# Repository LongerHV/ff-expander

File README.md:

# FF expander

ff-expander is a wireless expansion module for ffbeast based steering wheels.

Two Seeed XIAO ESP32-C6 boards linked over ESP-NOW: the **tx** board in the
wheel reads up to 10 buttons; the **rx** board in the base drives the parallel
inputs of two daisy-chained 74HC165s, which the MKS XDRIVE MINI reads over SPI.
Design notes: `docs/superpowers/specs/2026-11-23-ff-expander-design.md`.

## Wiring

| Button | TX pad (to GND) | RX pad (→ 74HC165) |
|-------:|-----------------|--------------------|
| 0 | D1 (wake) | D0 → chip 1 A |
| 1 | D2 (wake) | D1 → chip 1 B |
| 2 | D3 | D2 → chip 1 C |
| 3 | D4 | D3 → chip 1 D |
| 4 | D5 | D4 → chip 1 E |
| 5 | D6 | D5 → chip 1 F |
| 6 | D7 | D10 → chip 1 G |
| 7 | D8 | D7 → chip 1 H |
| 8 | D9 | D8 → chip 2 A |
| 9 | D10 | D9 → chip 2 B |

- TX buttons are wired between the pad and GND (internal pull-ups). D0 is free
  for a future battery-voltage divider. Buttons 0/1 wake the wheel from sleep.
- RX outputs are **low when pressed**, high when released or when the link is
  lost (`FFX_RX_PRESSED_LOW` in `include/ffx_config.h`). Tie unused 165 inputs
  high. Power the 165s from **3.3 V**.
- The RX user LED is lit while the link is up; the TX sleeps after 10 min idle.

### Proof of concept (no PCBs)

Envs `tx-poc` / `rx-poc` (`-DFFX_POC=1`) build a 4-button variant with the RX
wired straight to XDRIVE GPIO inputs, no 74HC165s:

| Button | TX pad (to GND) | RX pad → XDRIVE |
|-------:|-----------------|-----------------|
| 0 | D1 (wake) | D0 ─1k─► GPIO input |
| 1 | D2 (wake) | D1 ─1k─► GPIO input |
| 2 | D3 | D2 ─1k─► GPIO input |
| 3 | D4 | D3 ─1k─► GPIO input |

- XDRIVE inputs use their internal pull-ups, configured active-low. Check that
  they read released (> ~2.3 V) while the XIAO is held in its bootloader;
  otherwise add 10k pull-ups to 3V3.
- Power: header +5V → Schottky (SS14 / 1N5817) → XIAO `5V`, plus GND. The
  diode stops USB and the XDRIVE back-feeding each other.
- `python3 tools/link_test.py --buttons 4`

## Build, flash, test

```sh
nix develop                 # or nix-shell
pio test -e native          # unit tests for lib/ffx_core
pio run -e tx -t upload     # wheel board
pio run -e rx -t upload     # base board
python3 tools/link_test.py  # end-to-end test with both boards on USB
tools/lint.sh               # clang-format, ruff, nixfmt, actionlint
tools/check_hardware.sh     # generators in sync, ERC, DRC
```

CI (`.github/workflows/ci.yml`) runs the lint, unit tests, firmware build and
hardware checks on every push to `master` and on pull requests.

### Releases

Push a semver tag (`v1.2.3`, or `v1.2.3-rc.1` for a pre-release). The release
workflow reruns CI, then publishes a GitHub release with:

- `ff-expander-<tag>-tx.bin`, `ff-expander-<tag>-rx.bin`: complete flash
  images, written at offset 0:
  `esptool --chip esp32c6 write-flash 0x0 ff-expander-<tag>-tx.bin`
- `ff-expander-<tag>-{tx,rx}-gerbers.zip`: gerbers and drill files.

The same artifacts build locally with `tools/release.sh <version> dist`.

Board MACs (pairing) and serial ports are set in `include/ffx_config.h` and
`platformio.ini`.

### Console commands

TX: `p N` / `r N` press/release simulated button N, `m MASK` set all simulated
buttons, `mute MS` stop transmitting, `s` stats, `sleep`, `reboot`.
RX: `s` link stats. RX logs every output change as `RX t=… btn=0x… link=up|down`.

## License

- **Firmware, tools and scripts** (including `hardware/*.py`): MIT — see
  [LICENSE](LICENSE).
- **Hardware design** (`hardware/` KiCad files and libraries in `hardware/lib/`,
  `docs/hardware.md`): CERN Open Hardware Licence v2 – Strongly Reciprocal
  (CERN-OHL-S-2.0) — see [hardware/LICENSE](hardware/LICENSE).

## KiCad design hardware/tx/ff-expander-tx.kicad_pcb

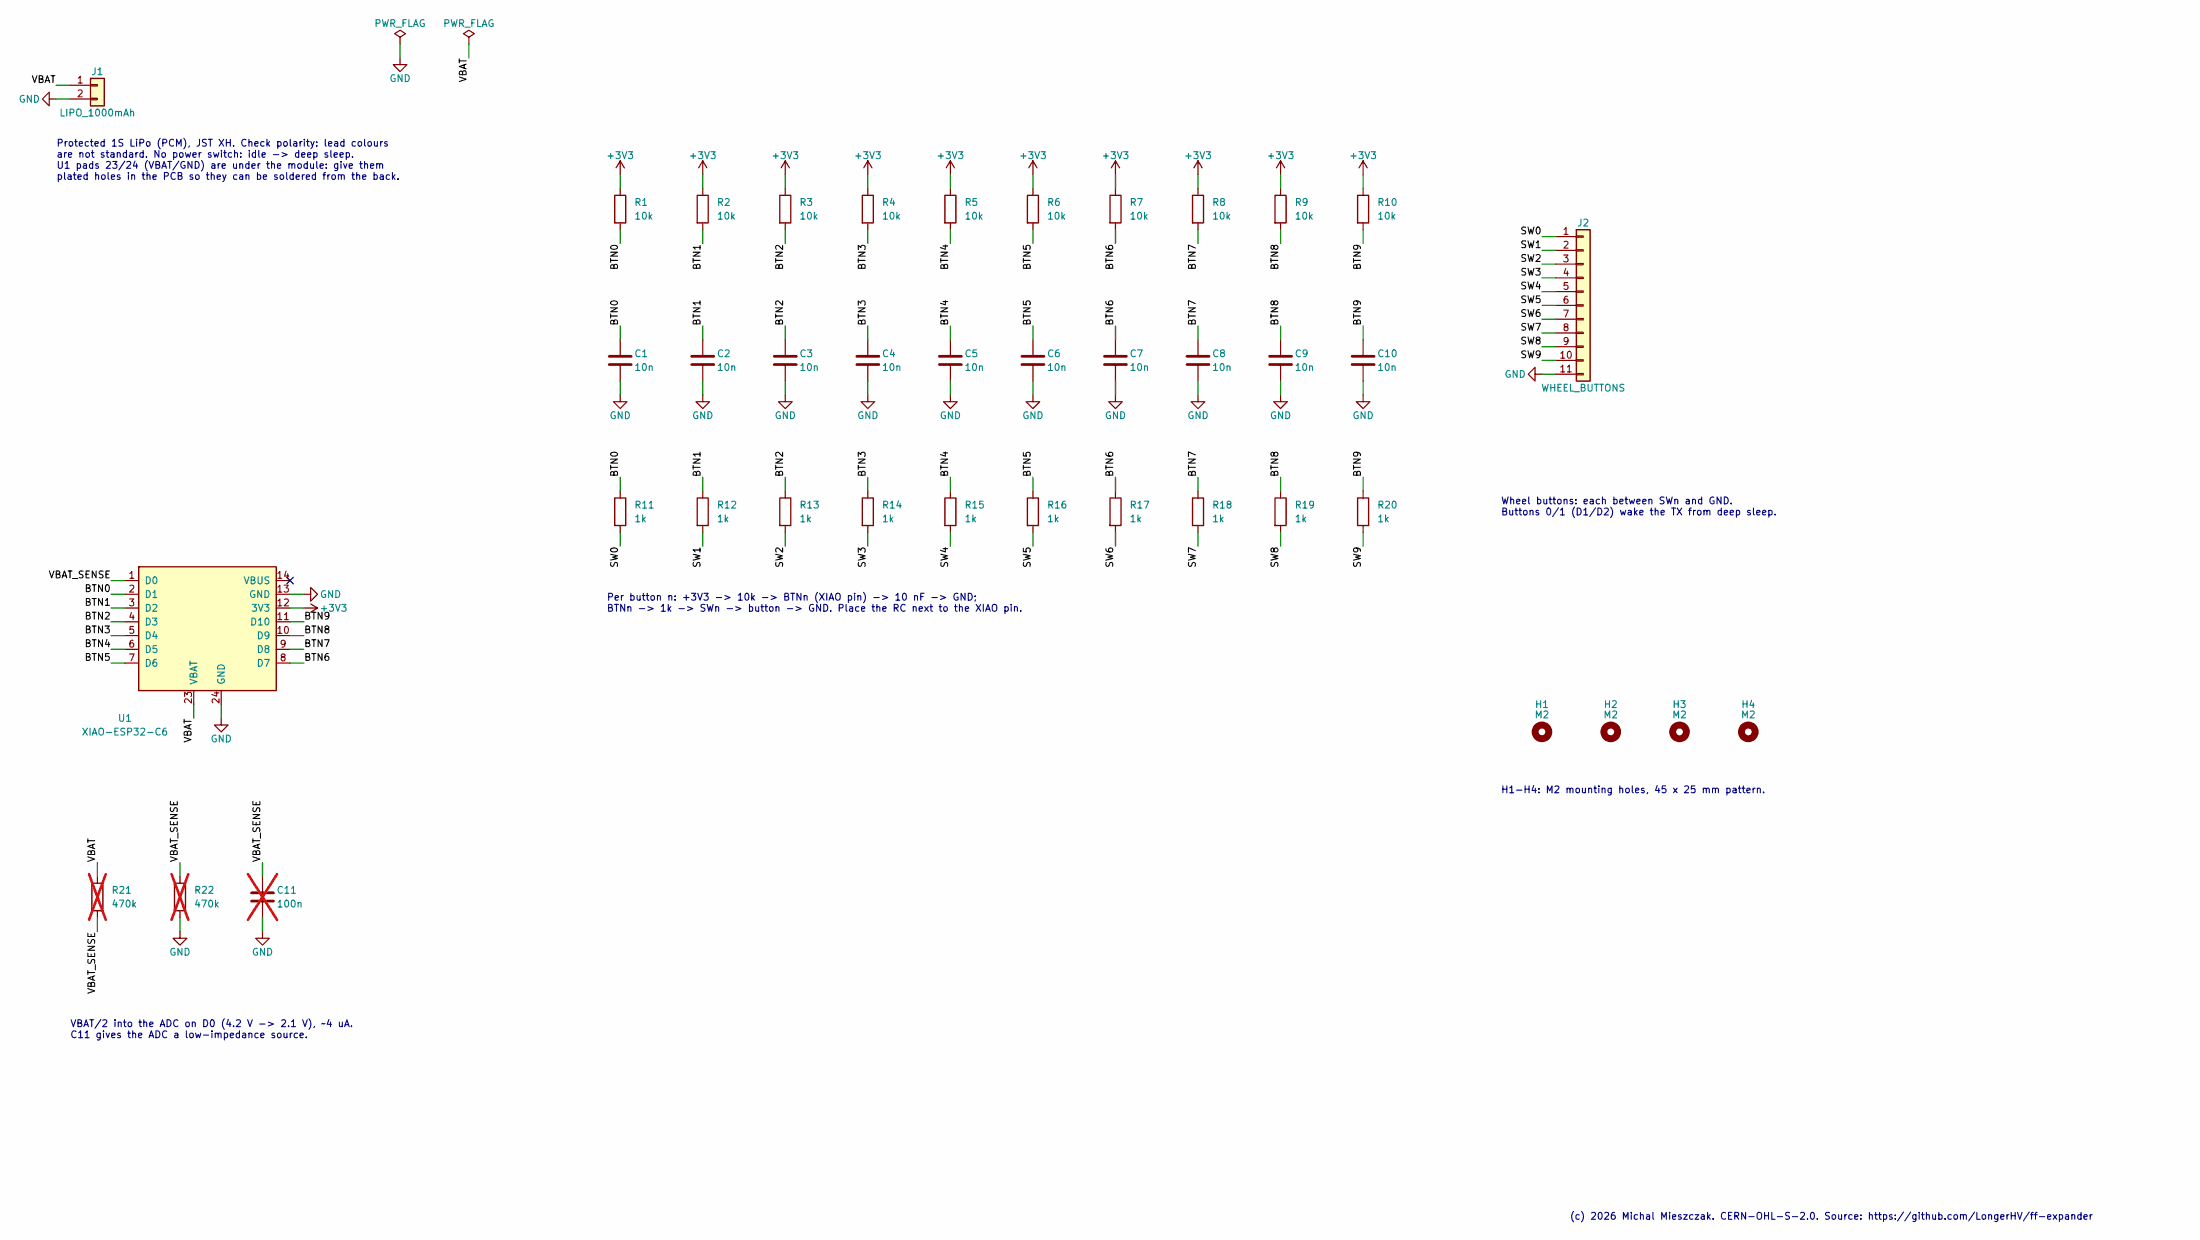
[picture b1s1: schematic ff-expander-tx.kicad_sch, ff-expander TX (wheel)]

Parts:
C1, C2, C3, C4, C5, C6, C7, C8, C9, C10: 10n; C_0805_2012Metric_Pad1.18x1.45mm_HandSolder
C11: 100n; C_0805_2012Metric_Pad1.18x1.45mm_HandSolder; not fitted
H1, H2, H3, H4: M2; MountingHole_2.2mm_M2
J1: LIPO_1000mAh; JST_XH_B2B-XH-A_1x02_P2.50mm_Vertical
J2: WHEEL_BUTTONS; JST_XH_B11B-XH-A_1x11_P2.50mm_Vertical
R1, R2, R3, R4, R5, R6, R7, R8, R9, R10: 10k; R_0805_2012Metric_Pad1.20x1.40mm_HandSolder
R11, R12, R13, R14, R15, R16, R17, R18, R19, R20: 1k; R_0805_2012Metric_Pad1.20x1.40mm_HandSolder
R21, R22: 470k; R_0805_2012Metric_Pad1.20x1.40mm_HandSolder; not fitted
U1: XIAO-ESP32-C6; XIAO_ESP32C6_HandSolder

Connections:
+3V3: R1.1, R2.1, R3.1, R4.1, R5.1, R6.1, R7.1, R8.1, R9.1, R10.1, U1.12 (3V3)
/BTN0: C1.1, R1.2, R11.1, U1.2 (D1)
/BTN1: C2.1, R2.2, R12.1, U1.3 (D2)
/BTN2: C3.1, R3.2, R13.1, U1.4 (D3)
/BTN3: C4.1, R4.2, R14.1, U1.5 (D4)
/BTN4: C5.1, R5.2, R15.1, U1.6 (D5)
/BTN5: C6.1, R6.2, R16.1, U1.7 (D6)
/BTN6: C7.1, R7.2, R17.1, U1.8 (D7)
/BTN7: C8.1, R8.2, R18.1, U1.9 (D8)
/BTN8: C9.1, R9.2, R19.1, U1.10 (D9)
/BTN9: C10.1, R10.2, R20.1, U1.11 (D10)
/SW0: J2.1, R11.2
/SW1: J2.2, R12.2
/SW2: J2.3, R13.2
/SW3: J2.4, R14.2
/SW4: J2.5, R15.2
/SW5: J2.6, R16.2
/SW6: J2.7, R17.2
/SW7: J2.8, R18.2
/SW8: J2.9, R19.2
/SW9: J2.10, R20.2
/VBAT: J1.1, R21.1, U1.23 (VBAT)
/VBAT_SENSE: C11.1, R21.2, R22.1, U1.1 (D0)
GND: C1.2, C2.2, C3.2, C4.2, C5.2, C6.2, C7.2, C8.2, C9.2, C10.2, C11.2, J1.2, J2.11, R22.2, U1.13 (GND), U1.24 (GND)

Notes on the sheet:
Protected 1S LiPo (PCM), JST XH. Check polarity: lead colours are not standard. No power switch: idle -> deep sleep. U1 pads 23/24 (VBAT/GND) are under the module: give them plated holes in the PCB so they can be soldered from the back.
VBAT/2 into the ADC on D0 (4.2 V -> 2.1 V), ~4 uA. C11 gives the ADC a low-impedance source.
Per button n: +3V3 -> 10k -> BTNn (XIAO pin) -> 10 nF -> GND; BTNn -> 1k -> SWn -> button -> GND. Place the RC next to the XIAO pin.
H1-H4: M2 mounting holes, 45 x 25 mm pattern.
Wheel buttons: each between SWn and GND. Buttons 0/1 (D1/D2) wake the TX from deep sleep.
(c) 2026 Michal Mieszczak. CERN-OHL-S-2.0. Source: https://github.com/LongerHV/ff-expander

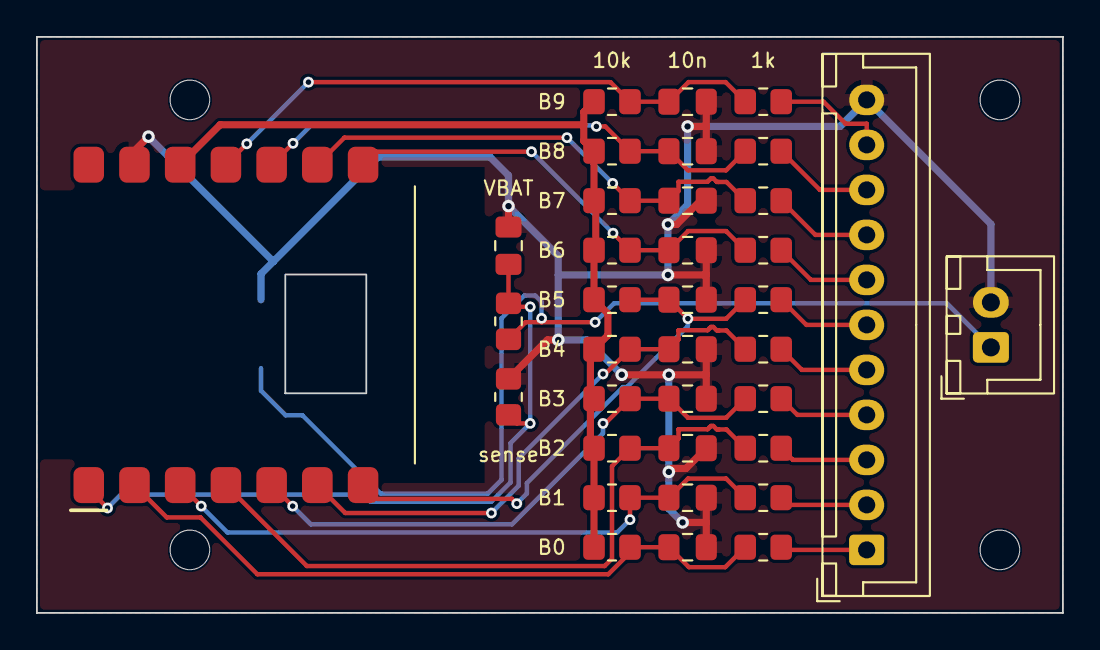
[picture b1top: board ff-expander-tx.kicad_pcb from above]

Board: 2 copper layers, 57.0 x 32.0 mm, 40 parts (0 on the bottom side), 24 nets.

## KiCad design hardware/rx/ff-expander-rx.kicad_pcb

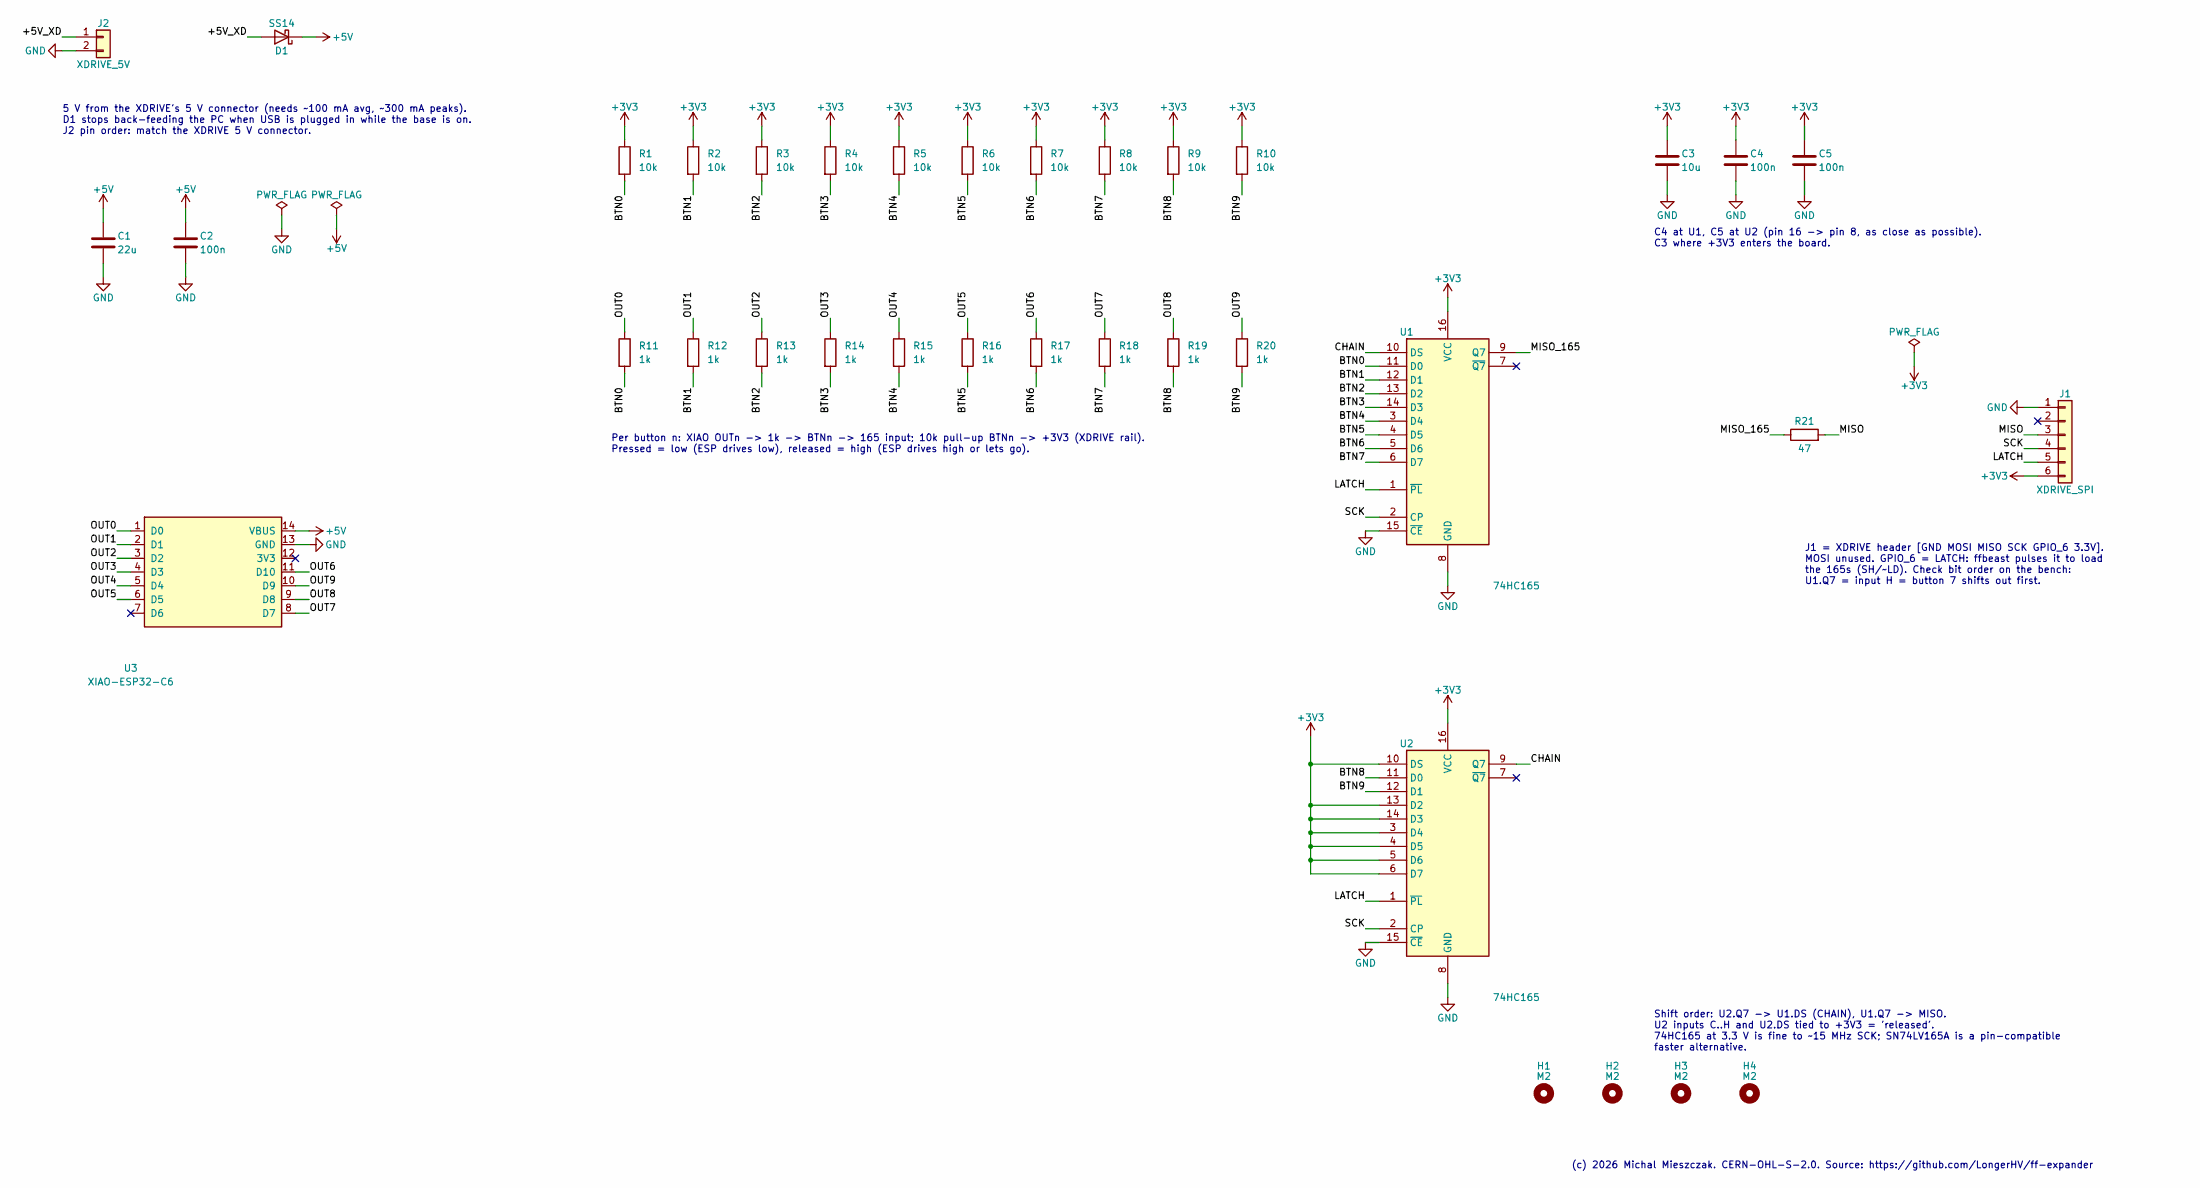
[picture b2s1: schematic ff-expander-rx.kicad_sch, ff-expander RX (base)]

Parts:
C1: 22u; C_0805_2012Metric_Pad1.18x1.45mm_HandSolder
C2, C4, C5: 100n; C_0805_2012Metric_Pad1.18x1.45mm_HandSolder
C3: 10u; C_0805_2012Metric_Pad1.18x1.45mm_HandSolder
D1: SS14; D_SMA_Handsoldering
H1, H2, H3, H4: M2; MountingHole_2.2mm_M2
J1: XDRIVE_SPI; JST_XH_B6B-XH-A_1x06_P2.50mm_Vertical
J2: XDRIVE_5V; JST_XH_B2B-XH-A_1x02_P2.50mm_Vertical
R1, R2, R3, R4, R5, R6, R7, R8, R9, R10: 10k; R_0805_2012Metric_Pad1.20x1.40mm_HandSolder
R11, R12, R13, R14, R15, R16, R17, R18, R19, R20: 1k; R_0805_2012Metric_Pad1.20x1.40mm_HandSolder
R21: 47; R_0805_2012Metric_Pad1.20x1.40mm_HandSolder
U1, U2: 74HC165; SOIC-16_3.9x9.9mm_P1.27mm
U3: XIAO-ESP32-C6; XIAO_ESP32C6_HandSolder_NoBat

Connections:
+3V3: C3.1, C4.1, C5.1, J1.6, R1.1, R2.1, R3.1, R4.1, R5.1, R6.1, R7.1, R8.1, R9.1, R10.1, U1.16 (VCC), U2.3 (D4), U2.4 (D5), U2.5 (D6), U2.6 (D7), U2.10 (DS), U2.13 (D2), U2.14 (D3), U2.16 (VCC)
+5V: C1.1, C2.1, D1.1 (K), U3.14 (VBUS)
/+5V_XD: D1.2 (A), J2.1
/BTN0: R1.2, R11.2, U1.11 (D0)
/BTN1: R2.2, R12.2, U1.12 (D1)
/BTN2: R3.2, R13.2, U1.13 (D2)
/BTN3: R4.2, R14.2, U1.14 (D3)
/BTN4: R5.2, R15.2, U1.3 (D4)
/BTN5: R6.2, R16.2, U1.4 (D5)
/BTN6: R7.2, R17.2, U1.5 (D6)
/BTN7: R8.2, R18.2, U1.6 (D7)
/BTN8: R9.2, R19.2, U2.11 (D0)
/BTN9: R10.2, R20.2, U2.12 (D1)
/CHAIN: U1.10 (DS), U2.9 (Q7)
/LATCH: J1.5, U1.1 (~PL), U2.1 (~PL)
/MISO: J1.3, R21.2
/MISO_165: R21.1, U1.9 (Q7)
/OUT0: R11.1, U3.1 (D0)
/OUT1: R12.1, U3.2 (D1)
/OUT2: R13.1, U3.3 (D2)
/OUT3: R14.1, U3.4 (D3)
/OUT4: R15.1, U3.5 (D4)
/OUT5: R16.1, U3.6 (D5)
/OUT6: R17.1, U3.11 (D10)
/OUT7: R18.1, U3.8 (D7)
/OUT8: R19.1, U3.9 (D8)
/OUT9: R20.1, U3.10 (D9)
/SCK: J1.4, U1.2 (CP), U2.2 (CP)
GND: C1.2, C2.2, C3.2, C4.2, C5.2, J1.1, J2.2, U1.8 (GND), U1.15 (~CE), U2.8 (GND), U2.15 (~CE), U3.13 (GND)

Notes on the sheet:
5 V from the XDRIVE's 5 V connector (needs ~100 mA avg, ~300 mA peaks). D1 stops back-feeding the PC when USB is plugged in while the base is on. J2 pin order: match the XDRIVE 5 V connector.
Per button n: XIAO OUTn -> 1k -> BTNn -> 165 input; 10k pull-up BTNn -> +3V3 (XDRIVE rail). Pressed = low (ESP drives low), released = high (ESP drives high or lets go).
C4 at U1, C5 at U2 (pin 16 -> pin 8, as close as possible). C3 where +3V3 enters the board.
J1 = XDRIVE header [GND MOSI MISO SCK GPIO_6 3.3V]. MOSI unused. GPIO_6 = LATCH: ffbeast pulses it to load the 165s (SH/~LD). Check bit order on the bench: U1.Q7 = input H = button 7 shifts out first.
Shift order: U2.Q7 -> U1.DS (CHAIN), U1.Q7 -> MISO. U2 inputs C..H and U2.DS tied to +3V3 = 'released'. 74HC165 at 3.3 V is fine to ~15 MHz SCK; SN74LV165A is a pin-compatible faster alternative.
(c) 2026 Michal Mieszczak. CERN-OHL-S-2.0. Source: https://github.com/LongerHV/ff-expander

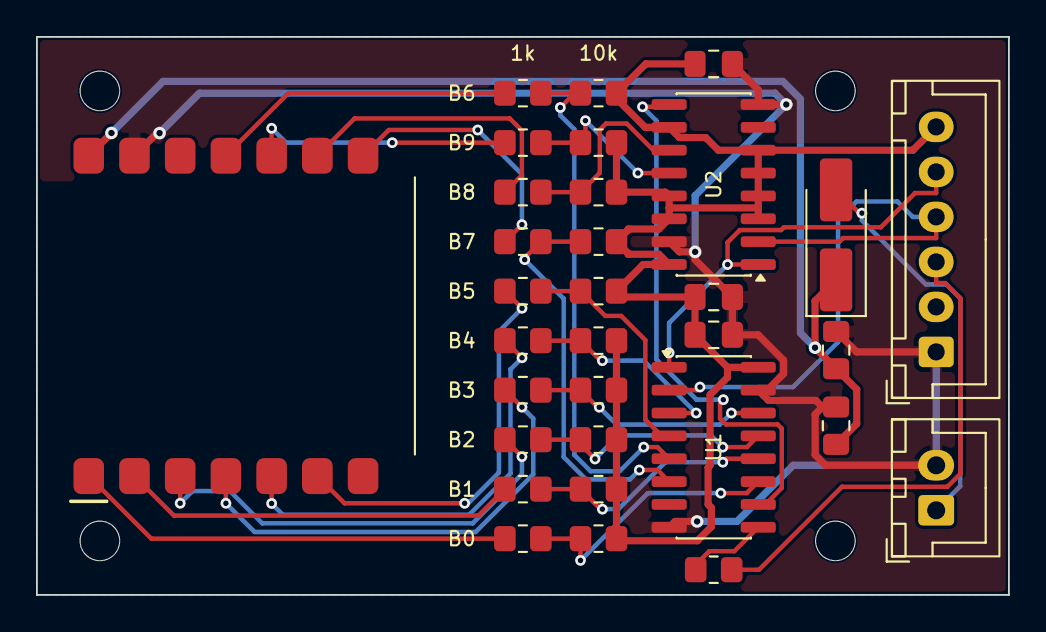
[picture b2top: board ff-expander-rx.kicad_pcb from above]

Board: 2 copper layers, 54.0 x 31.0 mm, 36 parts (0 on the bottom side), 29 nets.

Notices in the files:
hardware/rx/ff-expander-rx.kicad_pcb:
CERN-OHL-S-2.0  github.com/LongerHV/ff-expander
